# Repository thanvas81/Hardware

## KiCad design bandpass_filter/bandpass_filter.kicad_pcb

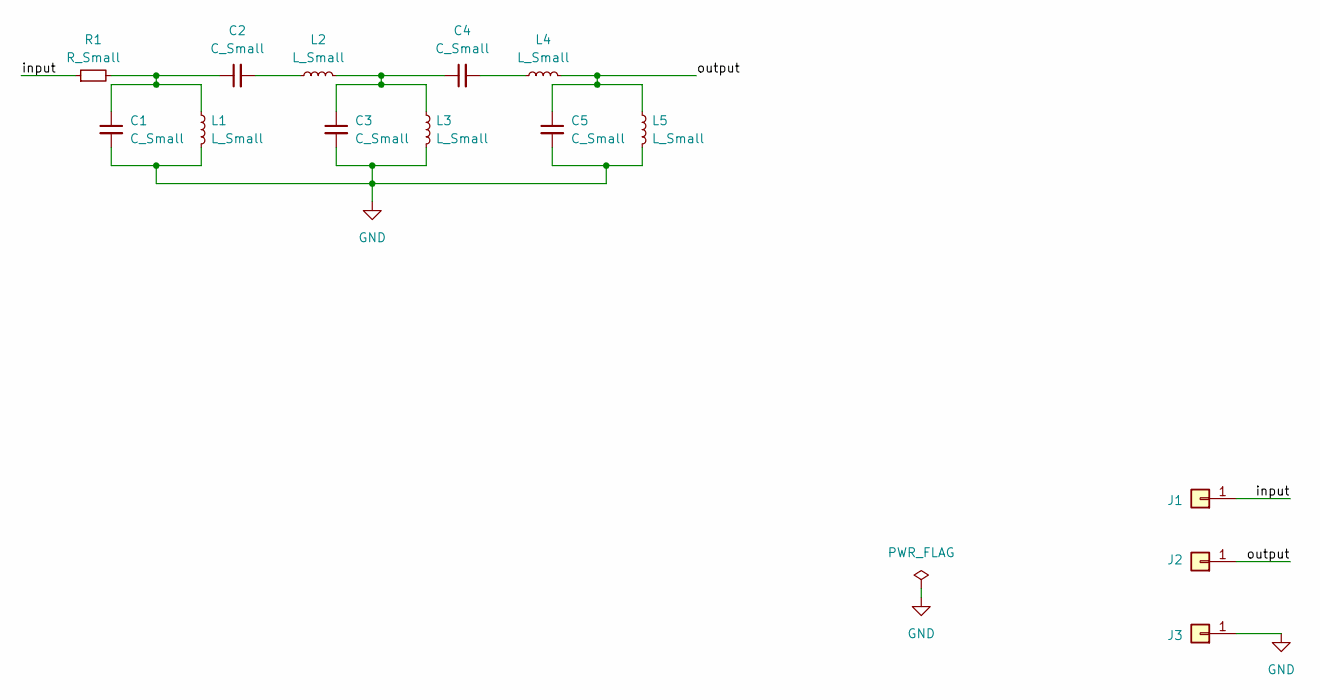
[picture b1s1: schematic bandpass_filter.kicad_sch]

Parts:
C1, C2, C3, C4, C5: C_Small; C_0603_1608Metric
J1, J2, J3: Conn_01x01; pad_smd_1.5x3
L1, L2, L3, L4, L5: L_Small; L_0603_1608Metric
R1: R_Small; R_0603_1608Metric

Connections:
/input: J1.1, R1.1
/output: C5.1, J2.1, L4.2, L5.1
GND: C1.2, C3.2, C5.2, J3.1, L1.2, L3.2, L5.2
unnamed: C1.1, C2.1, L1.1, R1.2
unnamed: C2.2, L2.1
unnamed: C3.1, C4.1, L2.2, L3.1
unnamed: C4.2, L4.1

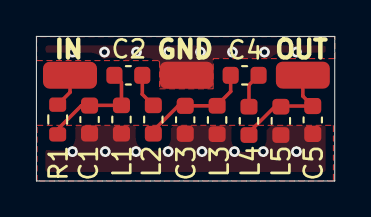
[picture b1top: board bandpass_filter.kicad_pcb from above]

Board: 2 copper layers, 16.6 x 8.0 mm, 14 parts (0 on the bottom side), 7 nets.

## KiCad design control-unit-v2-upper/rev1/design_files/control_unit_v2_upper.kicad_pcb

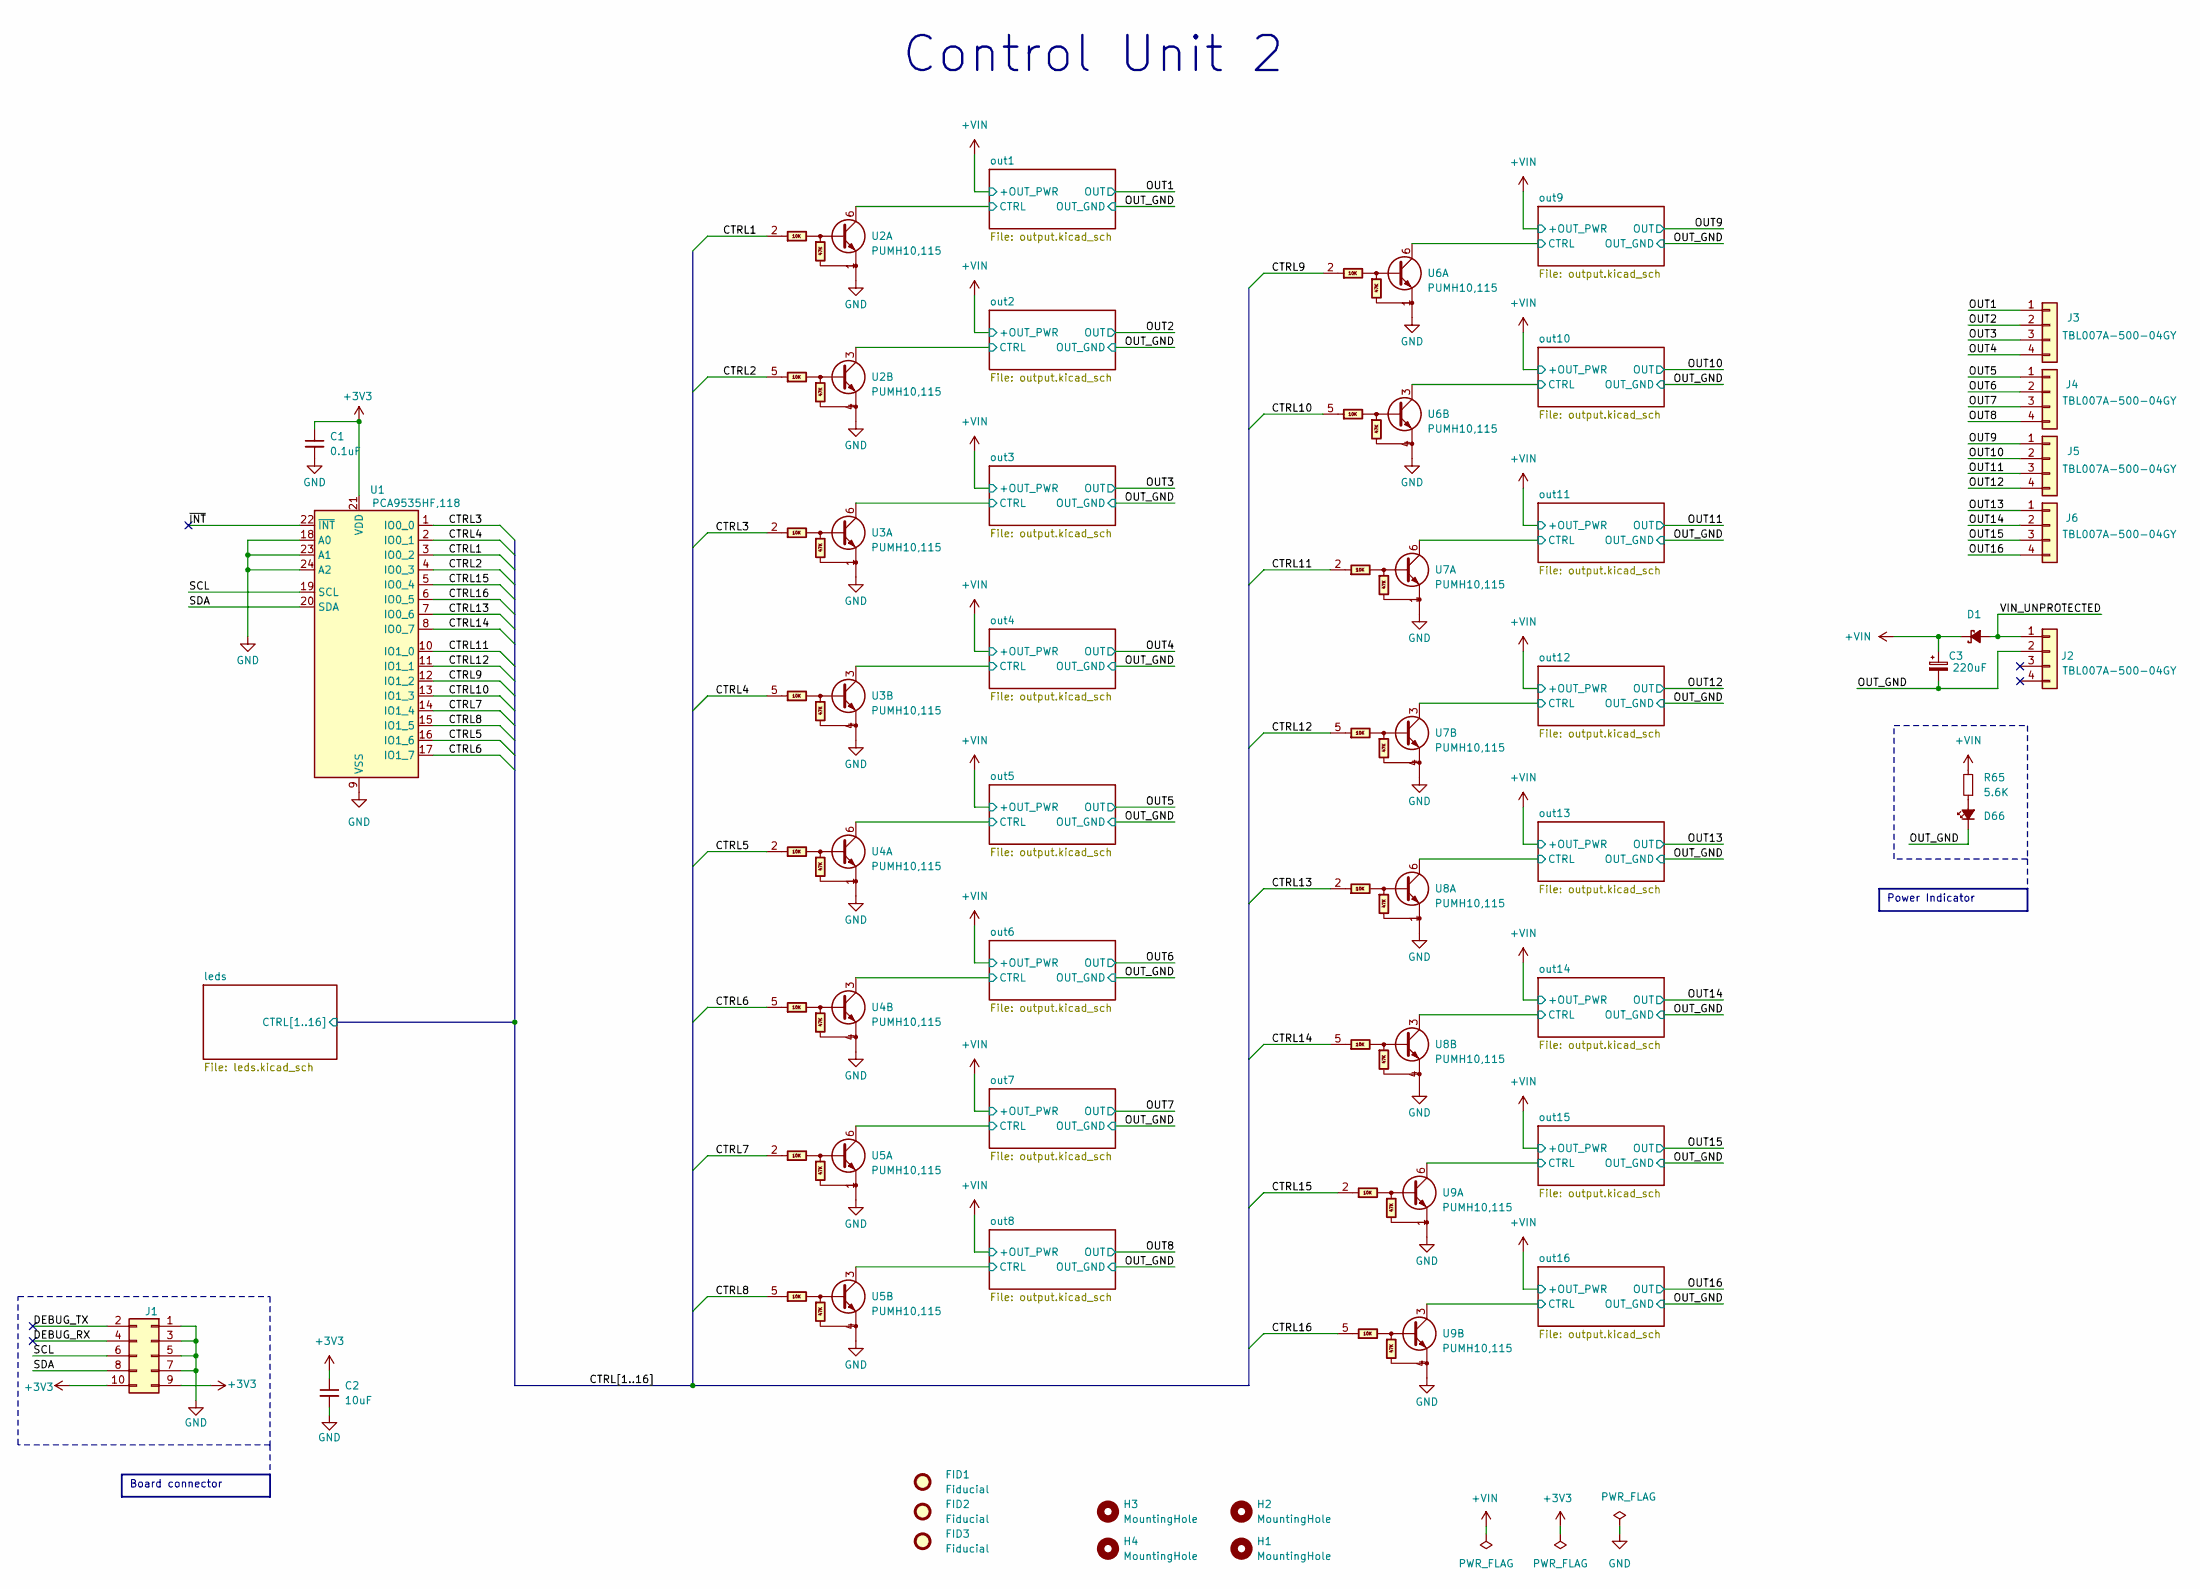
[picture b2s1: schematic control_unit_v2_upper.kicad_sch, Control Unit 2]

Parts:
C1: 0.1uF; C_0603_1608Metric; PartID 499
C2: 10uF; C_0805_2012Metric
C3: 220uF; CP_Elec_10x10
D1: D_PowerDI-123; PartID 501
D66: LED_Small_Filled; LED_0603_1608Metric; PartID 496
FID1, FID2, FID3: Fiducial; Fiducial_1mm_Mask2mm
H1, H2, H3, H4: MountingHole; MountingHole_3.2mm_M3_DIN965
J1: PinSocket_2x05_P2.54mm_Vertical_SMD
J2, J3, J4, J5, J6: TBL007A-500-04GY; TerminalBlock_IMO_203001M-4; PartID 1
R65: 5.6K; R_0402_1005Metric
U1: PCA9535HF,118; WQFN-24-1EP_4x4mm_P0.5mm_EP2.45x2.45mm; PartID 4
U2, U3, U4, U5, U6, U7, U8, U9: PUMH10,115; SOT-363_SC-70-6

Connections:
+3V3: C1.1, C2.1, J1.9, J1.10, U1.21 (VDD)
+VIN: C3.1, D1.1 (K), R65.2; also elsewhere on the board
/CTRL1: U1.3 (IO0_2), U2.2; also elsewhere on the board
/CTRL2: U1.4 (IO0_3), U2.5; also elsewhere on the board
/CTRL3: U1.1 (IO0_0), U3.2; also elsewhere on the board
/CTRL4: U1.2 (IO0_1), U3.5; also elsewhere on the board
/CTRL5: U1.16 (IO1_6), U4.2; also elsewhere on the board
/CTRL6: U1.17 (IO1_7), U4.5; also elsewhere on the board
/CTRL7: U1.14 (IO1_4), U5.2; also elsewhere on the board
/CTRL8: U1.15 (IO1_5), U5.5; also elsewhere on the board
/CTRL9: U1.12 (IO1_2), U6.2; also elsewhere on the board
/CTRL10: U1.13 (IO1_3), U6.5; also elsewhere on the board
/CTRL11: U1.10 (IO1_0), U7.2; also elsewhere on the board
/CTRL12: U1.11 (IO1_1), U7.5; also elsewhere on the board
/CTRL13: U1.7 (IO0_6), U8.2; also elsewhere on the board
/CTRL14: U1.8 (IO0_7), U8.5; also elsewhere on the board
/CTRL15: U1.5 (IO0_4), U9.2; also elsewhere on the board
/CTRL16: U1.6 (IO0_5), U9.5; also elsewhere on the board
/DEBUG_RX: J1.4
/DEBUG_TX: J1.2
/OUT1: J3.1; also elsewhere on the board
/OUT2: J3.2; also elsewhere on the board
/OUT3: J3.3; also elsewhere on the board
/OUT4: J3.4; also elsewhere on the board
/OUT5: J4.1; also elsewhere on the board
/OUT6: J4.2; also elsewhere on the board
/OUT7: J4.3; also elsewhere on the board
/OUT8: J4.4; also elsewhere on the board
/OUT9: J5.1; also elsewhere on the board
/OUT10: J5.2; also elsewhere on the board
/OUT11: J5.3; also elsewhere on the board
/OUT12: J5.4; also elsewhere on the board
/OUT13: J6.1; also elsewhere on the board
/OUT14: J6.2; also elsewhere on the board
/OUT15: J6.3; also elsewhere on the board
/OUT16: J6.4; also elsewhere on the board
/OUT_GND: C3.2, D66.1 (K), J2.2; also elsewhere on the board
/SCL: J1.6, U1.19 (SCL)
/SDA: J1.8, U1.20 (SDA)
/VIN_UNPROTECTED: D1.2 (A), J2.1
/out1/CTRL: U2.6; also elsewhere on the board
/out2/CTRL: U2.3; also elsewhere on the board
/out3/CTRL: U3.6; also elsewhere on the board
/out4/CTRL: U3.3; also elsewhere on the board
/out5/CTRL: U4.6; also elsewhere on the board
/out6/CTRL: U4.3; also elsewhere on the board
/out7/CTRL: U5.6; also elsewhere on the board
/out8/CTRL: U5.3; also elsewhere on the board
/out9/CTRL: U6.6; also elsewhere on the board
/out10/CTRL: U6.3; also elsewhere on the board
/out11/CTRL: U7.6; also elsewhere on the board
/out12/CTRL: U7.3; also elsewhere on the board
/out13/CTRL: U8.6; also elsewhere on the board
/out14/CTRL: U8.3; also elsewhere on the board
/out15/CTRL: U9.6; also elsewhere on the board
/out16/CTRL: U9.3; also elsewhere on the board
/~INT: U1.22 (~INT)
GND: C1.2, C2.2, J1.1, J1.3, J1.5, J1.7, U1.9 (VSS), U1.18 (A0), U1.23 (A1), U1.24 (A2), U1.25 (PAD), U2.1, U2.4, U3.1, U3.4, U4.1, U4.4, U5.1, U5.4, U6.1, U6.4, U7.1, U7.4, U8.1, U8.4, U9.1, U9.4; also elsewhere on the board
unnamed: D66.2 (A), R65.1

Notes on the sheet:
Power Indicator
Board connector
Control Unit 2

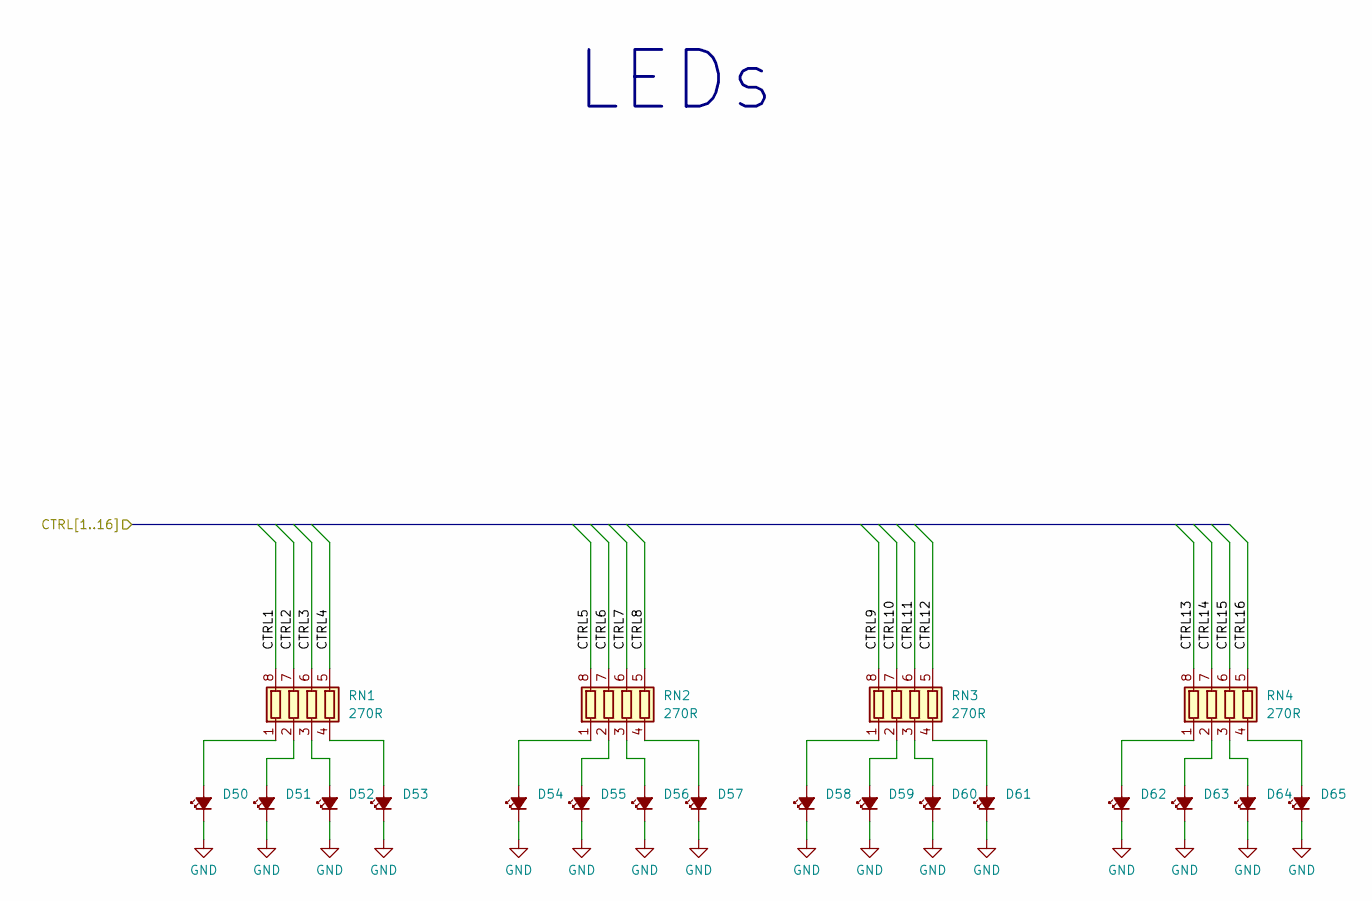
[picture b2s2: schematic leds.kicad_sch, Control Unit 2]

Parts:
D50, D51, D52, D53, D54, D55, D56, D57, D58, D59, D60, D61, D62, D63, D64, D65: LED_Small_Filled; LED_0603_1608Metric; PartID 496
RN1, RN2, RN3, RN4: 270R; R_Array_Concave_4x0603

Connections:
/CTRL1: RN1.8 (R1.2); also elsewhere on the board
/CTRL2: RN1.7 (R2.2); also elsewhere on the board
/CTRL3: RN1.6 (R3.2); also elsewhere on the board
/CTRL4: RN1.5 (R4.2); also elsewhere on the board
/CTRL5: RN2.8 (R1.2); also elsewhere on the board
/CTRL6: RN2.7 (R2.2); also elsewhere on the board
/CTRL7: RN2.6 (R3.2); also elsewhere on the board
/CTRL8: RN2.5 (R4.2); also elsewhere on the board
/CTRL9: RN3.8 (R1.2); also elsewhere on the board
/CTRL10: RN3.7 (R2.2); also elsewhere on the board
/CTRL11: RN3.6 (R3.2); also elsewhere on the board
/CTRL12: RN3.5 (R4.2); also elsewhere on the board
/CTRL13: RN4.8 (R1.2); also elsewhere on the board
/CTRL14: RN4.7 (R2.2); also elsewhere on the board
/CTRL15: RN4.6 (R3.2); also elsewhere on the board
/CTRL16: RN4.5 (R4.2); also elsewhere on the board
GND: D50.1 (K), D51.1 (K), D52.1 (K), D53.1 (K), D54.1 (K), D55.1 (K), D56.1 (K), D57.1 (K), D58.1 (K), D59.1 (K), D60.1 (K), D61.1 (K), D62.1 (K), D63.1 (K), D64.1 (K), D65.1 (K); also elsewhere on the board
unnamed: D50.2 (A), RN1.1 (R1.1)
unnamed: D51.2 (A), RN1.2 (R2.1)
unnamed: D52.2 (A), RN1.3 (R3.1)
unnamed: D53.2 (A), RN1.4 (R4.1)
unnamed: D54.2 (A), RN2.1 (R1.1)
unnamed: D55.2 (A), RN2.2 (R2.1)
unnamed: D56.2 (A), RN2.3 (R3.1)
unnamed: D57.2 (A), RN2.4 (R4.1)
unnamed: D58.2 (A), RN3.1 (R1.1)
unnamed: D59.2 (A), RN3.2 (R2.1)
unnamed: D60.2 (A), RN3.3 (R3.1)
unnamed: D61.2 (A), RN3.4 (R4.1)
unnamed: D62.2 (A), RN4.1 (R1.1)
unnamed: D63.2 (A), RN4.2 (R2.1)
unnamed: D64.2 (A), RN4.3 (R3.1)
unnamed: D65.2 (A), RN4.4 (R4.1)

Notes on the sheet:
LEDs

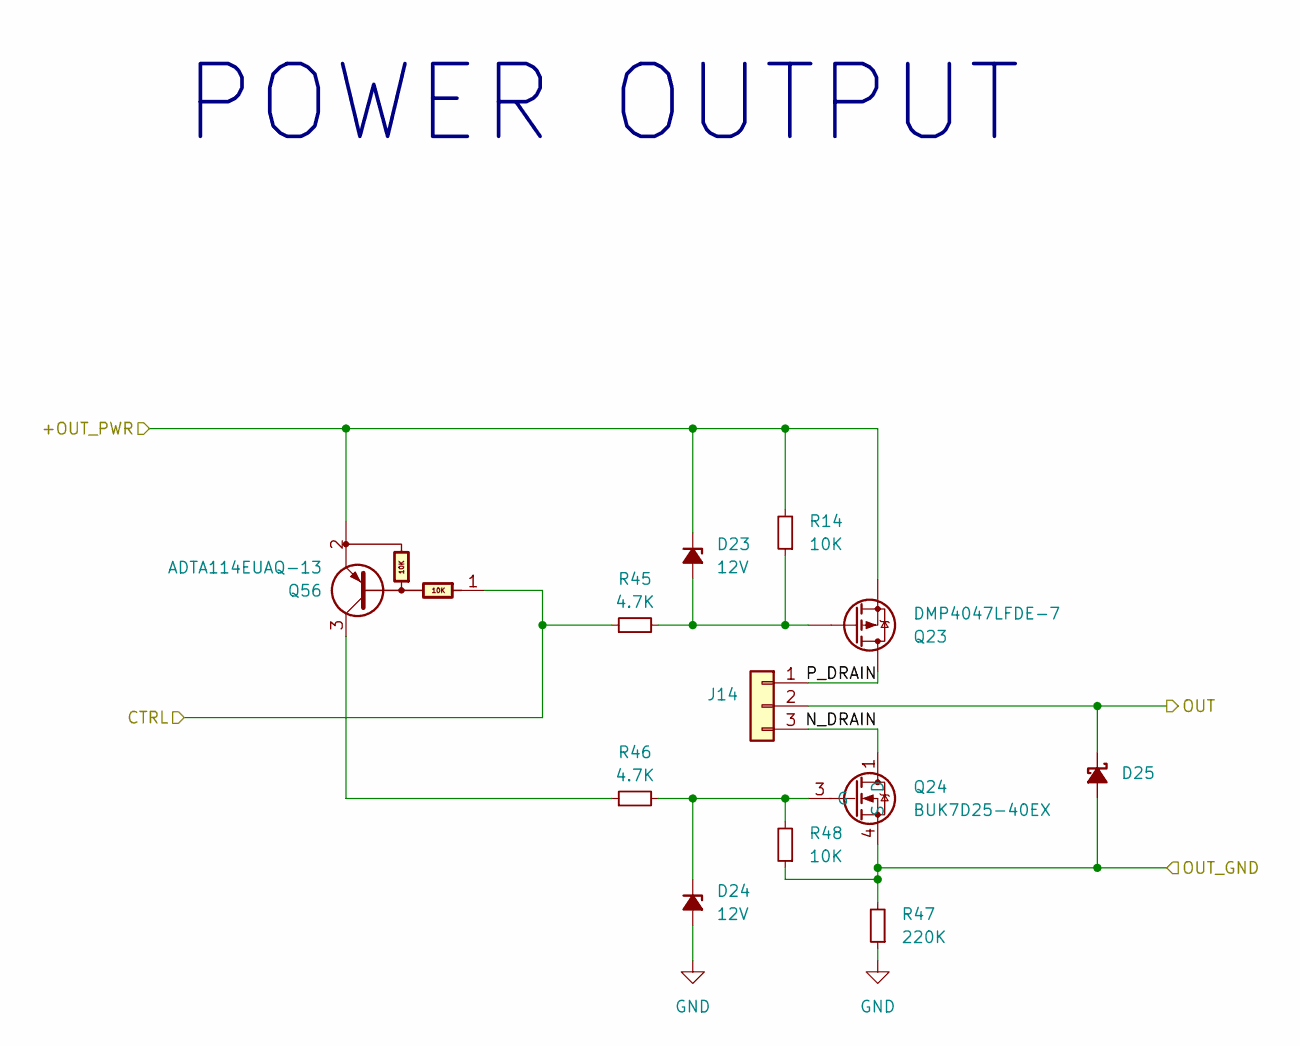
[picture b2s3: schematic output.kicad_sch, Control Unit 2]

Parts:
D23, D24: 12V; D_SOD-323
D25: D_PowerDI-123; PartID 501
J14: PinHeader_1x03_P2.54mm_Vertical
Q23: DMP4047LFDE-7; Diodes_Inc_U-DFN2020-6 (Type E)
Q24: BUK7D25-40EX; Diodes_UDFN2020-6_Type-F
Q56: ADTA114EUAQ-13; SOT-323_SC-70
R14, R48: 10K; R_0402_1005Metric
R45, R46: 4.7K; R_0402_1005Metric
R47: 220K; R_0402_1005Metric

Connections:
+VIN: D23.1 (K), Q23.3 (S), Q56.2, R14.2; also elsewhere on the board
/OUT8: D25.1 (K), J14.2; also elsewhere on the board
/OUT_GND: D25.2 (A), Q24.4 (S), Q24.8 (S), R47.2, R48.1; also elsewhere on the board
/out8/CTRL: Q56.1, R45.1; also elsewhere on the board
/out8/N_DRAIN: J14.3, Q24.1 (D), Q24.2 (D), Q24.5 (D), Q24.6 (D), Q24.7 (D)
/out8/P_DRAIN: J14.1, Q23.1 (D)
GND: D24.2 (A), R47.1; also elsewhere on the board
unnamed: D23.2 (A), Q23.2 (G), R14.1, R45.2
unnamed: D24.1 (K), Q24.3 (G), R46.2, R48.2
unnamed: Q56.3, R46.1

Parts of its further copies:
D2, D3, D5, D6, D8, D9, D11, D12, D14, D15, D17, D18, D20, D21, D26, D27, D29, D30, D32, D33, D35, D36, D38, D39, D41, D42, D44, D45, D47, D48: 12V; D_SOD-323
D4, D7, D10, D13, D16, D19, D22, D28, D31, D34, D37, D40, D43, D46, D49: D_PowerDI-123; PartID 501
J7, J8, J9, J10, J11, J12, J13, J15, J16, J17, J18, J19, J20, J21, J22: PinHeader_1x03_P2.54mm_Vertical
Q1, Q50, Q51, Q52, Q53, Q54, Q55, Q57, Q58, Q59, Q60, Q61, Q62, Q63, Q64: ADTA114EUAQ-13; SOT-323_SC-70
Q2, Q5, Q8, Q11, Q14, Q17, Q20, Q26, Q29, Q32, Q35, Q38, Q41, Q44, Q47: DMP4047LFDE-7; Diodes_Inc_U-DFN2020-6 (Type E)
Q3, Q6, Q9, Q12, Q15, Q18, Q21, Q27, Q30, Q33, Q36, Q39, Q42, Q45, Q48: BUK7D25-40EX; Diodes_UDFN2020-6_Type-F
R1, R2, R9, R10, R15, R16, R21, R22, R27, R28, R33, R34, R39, R40, R51, R52, R57, R58, R63, R64, R69, R70, R75, R76, R81, R82, R87, R88, R93, R94: 4.7K; R_0402_1005Metric
R3, R4, R5, R6, R7, R8, R11, R12, R13, R17, R18, R19, R20, R23, R24, R25, R26, R29, R30, R31, R36, R42, R54, R60, R66, R72, R78, R84, R90, R96: 10K; R_0402_1005Metric
R32, R35, R37, R38, R41, R43, R44, R49, R50, R53, R55, R56, R59, R61, R62: 220K; R_0402_1005Metric

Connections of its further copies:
+VIN: D2.1 (K), D5.1 (K), D8.1 (K), D11.1 (K), D14.1 (K), D17.1 (K), D20.1 (K), D26.1 (K), D29.1 (K), D32.1 (K), D35.1 (K), D38.1 (K), D41.1 (K), D44.1 (K), D47.1 (K), Q1.2, Q2.3 (S), Q5.3 (S), Q8.3 (S), Q11.3 (S), Q14.3 (S), Q17.3 (S), Q20.3 (S), Q26.3 (S), Q29.3 (S), Q32.3 (S), Q35.3 (S), Q38.3 (S), Q41.3 (S), Q44.3 (S), Q47.3 (S), Q50.2, Q51.2, Q52.2, Q53.2, Q54.2, Q55.2, Q57.2, Q58.2, Q59.2, Q60.2, Q61.2, Q62.2, Q63.2, Q64.2, R3.2, R5.2, R6.2, R7.2, R8.2, R11.2, R13.2, R17.2, R19.2, R20.2, R23.2, R25.2, R26.2, R29.2, R31.2; also elsewhere on the board
/OUT1: D4.1 (K), J7.2; also elsewhere on the board
/OUT2: D7.1 (K), J8.2; also elsewhere on the board
/OUT3: D10.1 (K), J9.2; also elsewhere on the board
/OUT4: D13.1 (K), J10.2; also elsewhere on the board
/OUT5: D16.1 (K), J11.2; also elsewhere on the board
/OUT6: D19.1 (K), J12.2; also elsewhere on the board
/OUT7: D22.1 (K), J13.2; also elsewhere on the board
/OUT9: D28.1 (K), J15.2; also elsewhere on the board
/OUT10: D31.1 (K), J16.2; also elsewhere on the board
/OUT11: D34.1 (K), J17.2; also elsewhere on the board
/OUT12: D37.1 (K), J18.2; also elsewhere on the board
/OUT13: D40.1 (K), J19.2; also elsewhere on the board
/OUT14: D43.1 (K), J20.2; also elsewhere on the board
/OUT15: D46.1 (K), J21.2; also elsewhere on the board
/OUT16: D49.1 (K), J22.2; also elsewhere on the board
/OUT_GND: D4.2 (A), D7.2 (A), D10.2 (A), D13.2 (A), D16.2 (A), D19.2 (A), D22.2 (A), D28.2 (A), D31.2 (A), D34.2 (A), D37.2 (A), D40.2 (A), D43.2 (A), D46.2 (A), D49.2 (A), Q3.4 (S), Q3.8 (S), Q6.4 (S), Q6.8 (S), Q9.4 (S), Q9.8 (S), Q12.4 (S), Q12.8 (S), Q15.4 (S), Q15.8 (S), Q18.4 (S), Q18.8 (S), Q21.4 (S), Q21.8 (S), Q27.4 (S), Q27.8 (S), Q30.4 (S), Q30.8 (S), Q33.4 (S), Q33.8 (S), Q36.4 (S), Q36.8 (S), Q39.4 (S), Q39.8 (S), Q42.4 (S), Q42.8 (S), Q45.4 (S), Q45.8 (S), Q48.4 (S), Q48.8 (S), R4.1, R12.1, R18.1, R24.1, R30.1, R32.2, R35.2, R36.1, R37.2, R38.2, R41.2, R42.1, R43.2, R44.2, R49.2, R50.2, R53.2, R54.1, R55.2, R56.2, R59.2, R60.1, R61.2, R62.2, R66.1, R72.1, R78.1, R84.1, R90.1, R96.1; also elsewhere on the board
/out1/CTRL: Q1.1, R1.1; also elsewhere on the board
/out1/N_DRAIN: J7.3, Q3.1 (D), Q3.2 (D), Q3.5 (D), Q3.6 (D), Q3.7 (D)
/out1/P_DRAIN: J7.1, Q2.1 (D)
/out2/CTRL: Q51.1, R9.1; also elsewhere on the board
/out2/N_DRAIN: J8.3, Q6.1 (D), Q6.2 (D), Q6.5 (D), Q6.6 (D), Q6.7 (D)
/out2/P_DRAIN: J8.1, Q5.1 (D)
/out3/CTRL: Q50.1, R15.1; also elsewhere on the board
/out3/N_DRAIN: J9.3, Q9.1 (D), Q9.2 (D), Q9.5 (D), Q9.6 (D), Q9.7 (D)
/out3/P_DRAIN: J9.1, Q8.1 (D)
/out4/CTRL: Q52.1, R21.1; also elsewhere on the board
/out4/N_DRAIN: J10.3, Q12.1 (D), Q12.2 (D), Q12.5 (D), Q12.6 (D), Q12.7 (D)
/out4/P_DRAIN: J10.1, Q11.1 (D)
/out5/CTRL: Q53.1, R27.1; also elsewhere on the board
/out5/N_DRAIN: J11.3, Q15.1 (D), Q15.2 (D), Q15.5 (D), Q15.6 (D), Q15.7 (D)
/out5/P_DRAIN: J11.1, Q14.1 (D)
/out6/CTRL: Q54.1, R33.1; also elsewhere on the board
/out6/N_DRAIN: J12.3, Q18.1 (D), Q18.2 (D), Q18.5 (D), Q18.6 (D), Q18.7 (D)
/out6/P_DRAIN: J12.1, Q17.1 (D)
/out7/CTRL: Q55.1, R39.1; also elsewhere on the board
/out7/N_DRAIN: J13.3, Q21.1 (D), Q21.2 (D), Q21.5 (D), Q21.6 (D), Q21.7 (D)
/out7/P_DRAIN: J13.1, Q20.1 (D)
/out9/CTRL: Q57.1, R51.1; also elsewhere on the board
/out9/N_DRAIN: J15.3, Q27.1 (D), Q27.2 (D), Q27.5 (D), Q27.6 (D), Q27.7 (D)
/out9/P_DRAIN: J15.1, Q26.1 (D)
/out10/CTRL: Q58.1, R57.1; also elsewhere on the board
/out10/N_DRAIN: J16.3, Q30.1 (D), Q30.2 (D), Q30.5 (D), Q30.6 (D), Q30.7 (D)
/out10/P_DRAIN: J16.1, Q29.1 (D)
/out11/CTRL: Q59.1, R63.1; also elsewhere on the board
/out11/N_DRAIN: J17.3, Q33.1 (D), Q33.2 (D), Q33.5 (D), Q33.6 (D), Q33.7 (D)
/out11/P_DRAIN: J17.1, Q32.1 (D)
/out12/CTRL: Q60.1, R69.1; also elsewhere on the board
/out12/N_DRAIN: J18.3, Q36.1 (D), Q36.2 (D), Q36.5 (D), Q36.6 (D), Q36.7 (D)
/out12/P_DRAIN: J18.1, Q35.1 (D)
/out13/CTRL: Q61.1, R75.1; also elsewhere on the board
/out13/N_DRAIN: J19.3, Q39.1 (D), Q39.2 (D), Q39.5 (D), Q39.6 (D), Q39.7 (D)
/out13/P_DRAIN: J19.1, Q38.1 (D)
/out14/CTRL: Q62.1, R81.1; also elsewhere on the board
/out14/N_DRAIN: J20.3, Q42.1 (D), Q42.2 (D), Q42.5 (D), Q42.6 (D), Q42.7 (D)
/out14/P_DRAIN: J20.1, Q41.1 (D)
/out15/CTRL: Q63.1, R87.1; also elsewhere on the board
/out15/N_DRAIN: J21.3, Q45.1 (D), Q45.2 (D), Q45.5 (D), Q45.6 (D), Q45.7 (D)
/out15/P_DRAIN: J21.1, Q44.1 (D)
/out16/CTRL: Q64.1, R93.1; also elsewhere on the board
/out16/N_DRAIN: J22.3, Q48.1 (D), Q48.2 (D), Q48.5 (D), Q48.6 (D), Q48.7 (D)
/out16/P_DRAIN: J22.1, Q47.1 (D)
GND: D3.2 (A), D6.2 (A), D9.2 (A), D12.2 (A), D15.2 (A), D18.2 (A), D21.2 (A), D27.2 (A), D30.2 (A), D33.2 (A), D36.2 (A), D39.2 (A), D42.2 (A), D45.2 (A), D48.2 (A), R32.1, R35.1, R37.1, R38.1, R41.1, R43.1, R44.1, R49.1, R50.1, R53.1, R55.1, R56.1, R59.1, R61.1, R62.1; also elsewhere on the board
unnamed: D2.2 (A), Q2.2 (G), R1.2, R3.1
unnamed: D3.1 (K), Q3.3 (G), R2.2, R4.2
unnamed: D5.2 (A), Q5.2 (G), R6.1, R9.2
unnamed: D6.1 (K), Q6.3 (G), R10.2, R12.2
unnamed: D8.2 (A), Q8.2 (G), R5.1, R15.2
unnamed: D9.1 (K), Q9.3 (G), R16.2, R18.2
unnamed: D11.2 (A), Q11.2 (G), R7.1, R21.2
unnamed: D12.1 (K), Q12.3 (G), R22.2, R24.2
unnamed: D14.2 (A), Q14.2 (G), R8.1, R27.2
unnamed: D15.1 (K), Q15.3 (G), R28.2, R30.2
unnamed: D17.2 (A), Q17.2 (G), R11.1, R33.2
unnamed: D18.1 (K), Q18.3 (G), R34.2, R36.2
unnamed: D20.2 (A), Q20.2 (G), R13.1, R39.2
unnamed: D21.1 (K), Q21.3 (G), R40.2, R42.2
unnamed: D26.2 (A), Q26.2 (G), R17.1, R51.2
unnamed: D27.1 (K), Q27.3 (G), R52.2, R54.2
unnamed: D29.2 (A), Q29.2 (G), R19.1, R57.2
unnamed: D30.1 (K), Q30.3 (G), R58.2, R60.2
unnamed: D32.2 (A), Q32.2 (G), R20.1, R63.2
unnamed: D33.1 (K), Q33.3 (G), R64.2, R66.2
unnamed: D35.2 (A), Q35.2 (G), R23.1, R69.2
unnamed: D36.1 (K), Q36.3 (G), R70.2, R72.2
unnamed: D38.2 (A), Q38.2 (G), R25.1, R75.2
unnamed: D39.1 (K), Q39.3 (G), R76.2, R78.2
unnamed: D41.2 (A), Q41.2 (G), R26.1, R81.2
unnamed: D42.1 (K), Q42.3 (G), R82.2, R84.2
unnamed: D44.2 (A), Q44.2 (G), R29.1, R87.2
unnamed: D45.1 (K), Q45.3 (G), R88.2, R90.2
unnamed: D47.2 (A), Q47.2 (G), R31.1, R93.2
unnamed: D48.1 (K), Q48.3 (G), R94.2, R96.2
unnamed: Q1.3, R2.1
unnamed: Q50.3, R16.1
unnamed: Q51.3, R10.1
unnamed: Q52.3, R22.1
unnamed: Q53.3, R28.1
unnamed: Q54.3, R34.1
unnamed: Q55.3, R40.1
unnamed: Q57.3, R52.1
unnamed: Q58.3, R58.1
unnamed: Q59.3, R64.1
unnamed: Q60.3, R70.1
unnamed: Q61.3, R76.1
unnamed: Q62.3, R82.1
unnamed: Q63.3, R88.1
unnamed: Q64.3, R94.1

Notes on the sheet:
POWER OUTPUT

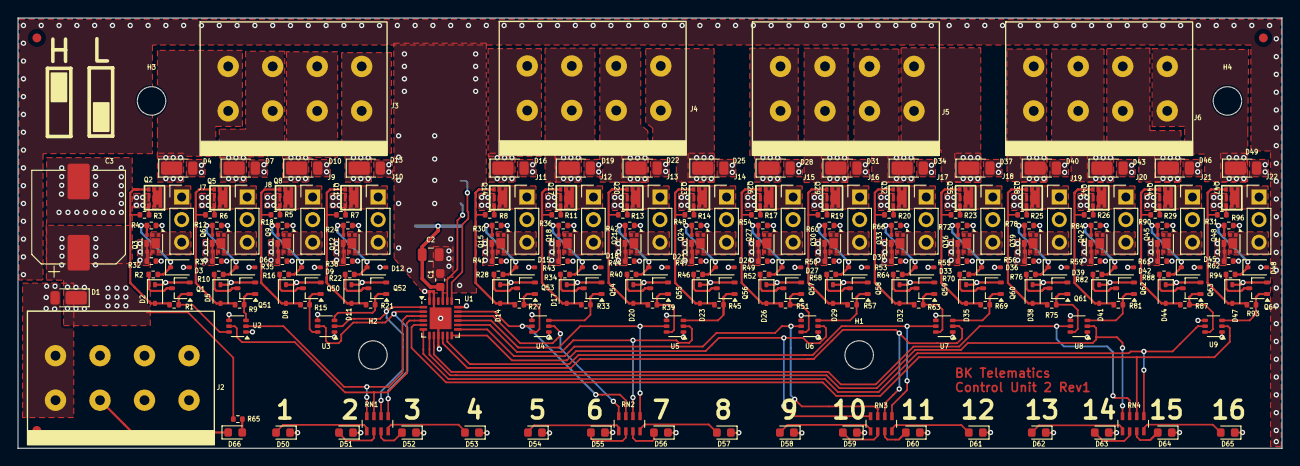
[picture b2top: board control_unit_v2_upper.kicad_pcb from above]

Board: 4 copper layers, 142.0 x 48.3 mm, 240 parts (1 on the bottom side), 152 nets.

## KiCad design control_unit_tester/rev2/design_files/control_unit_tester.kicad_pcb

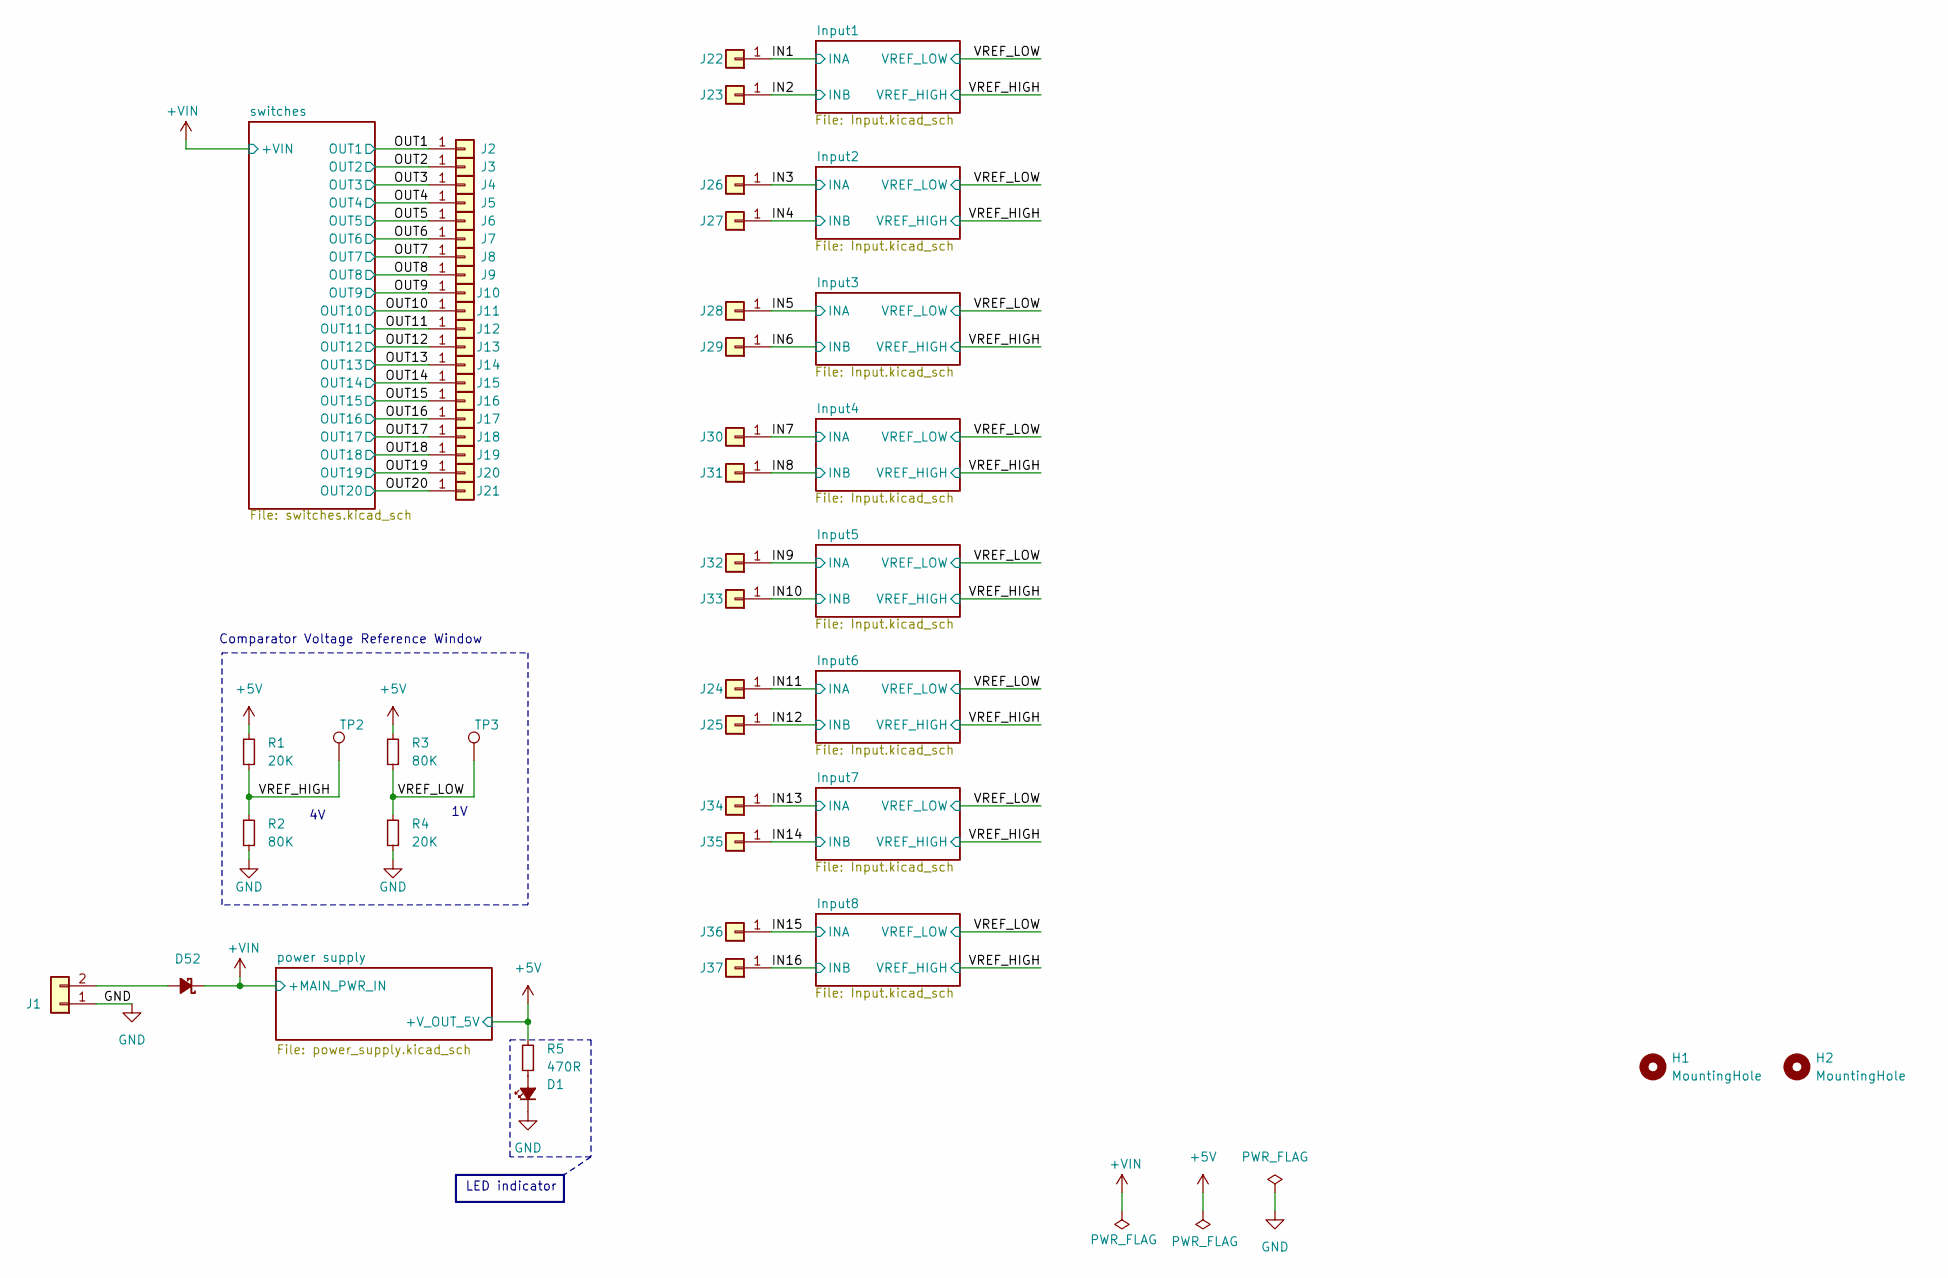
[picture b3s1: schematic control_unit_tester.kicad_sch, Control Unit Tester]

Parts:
D1: LED 0805 SMD; LED_0805_2012Metric
D52: SBR3U60P1Q-7; D_PowerDI-123; PartkeeprID 43
H1, H2: MountingHole; MountingHole_3.2mm_M3_DIN965
J1: Conn_01x02; TerminalBlock_4Ucon_1x02_P3.50mm_Horizontal
J2, J3, J4, J5, J6, J7, J8, J9, J10, J11, J12, J13, J14, J15, J16, J17, J18, J19, J20, J21, J22, J23, J24, J25, J26, J27, J28, J29, J30, J31, J32, J33, J34, J35, J36, J37: T.H. Pad; Hole_pad_1.5x3_round
R1, R4: 20Κ; R_0805_2012Metric
R2, R3: 80Κ; R_0805_2012Metric
R5: 470R; R_0805_2012Metric
TP2, TP3: TestPoint; TestPoint_Pad_D1.5mm

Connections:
+5V: R1.1, R3.1, R5.2; also elsewhere on the board
+VIN: D52.1 (K); also elsewhere on the board
/IN1: J22.1; also elsewhere on the board
/IN2: J23.1; also elsewhere on the board
/IN3: J26.1; also elsewhere on the board
/IN4: J27.1; also elsewhere on the board
/IN5: J28.1; also elsewhere on the board
/IN6: J29.1; also elsewhere on the board
/IN7: J30.1; also elsewhere on the board
/IN8: J31.1; also elsewhere on the board
/IN9: J32.1; also elsewhere on the board
/IN10: J33.1; also elsewhere on the board
/IN11: J24.1; also elsewhere on the board
/IN12: J25.1; also elsewhere on the board
/IN13: J34.1; also elsewhere on the board
/IN14: J35.1; also elsewhere on the board
/IN15: J36.1; also elsewhere on the board
/IN16: J37.1; also elsewhere on the board
/OUT1: J2.1; also elsewhere on the board
/OUT2: J3.1; also elsewhere on the board
/OUT3: J4.1; also elsewhere on the board
/OUT4: J5.1; also elsewhere on the board
/OUT5: J6.1; also elsewhere on the board
/OUT6: J7.1; also elsewhere on the board
/OUT7: J8.1; also elsewhere on the board
/OUT8: J9.1; also elsewhere on the board
/OUT9: J10.1; also elsewhere on the board
/OUT10: J11.1; also elsewhere on the board
/OUT11: J12.1; also elsewhere on the board
/OUT12: J13.1; also elsewhere on the board
/OUT13: J14.1; also elsewhere on the board
/OUT14: J15.1; also elsewhere on the board
/OUT15: J16.1; also elsewhere on the board
/OUT16: J17.1; also elsewhere on the board
/OUT17: J18.1; also elsewhere on the board
/OUT18: J19.1; also elsewhere on the board
/OUT19: J20.1; also elsewhere on the board
/OUT20: J21.1; also elsewhere on the board
/VREF_HIGH: R1.2, R2.1, TP2.1; also elsewhere on the board
/VREF_LOW: R3.2, R4.1, TP3.1; also elsewhere on the board
GND: D1.1 (K), J1.1, R2.2, R4.2; also elsewhere on the board
unnamed: D1.2 (A), R5.1
unnamed: D52.2 (A), J1.2

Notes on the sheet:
LED indicator
Comparator Voltage Reference Window

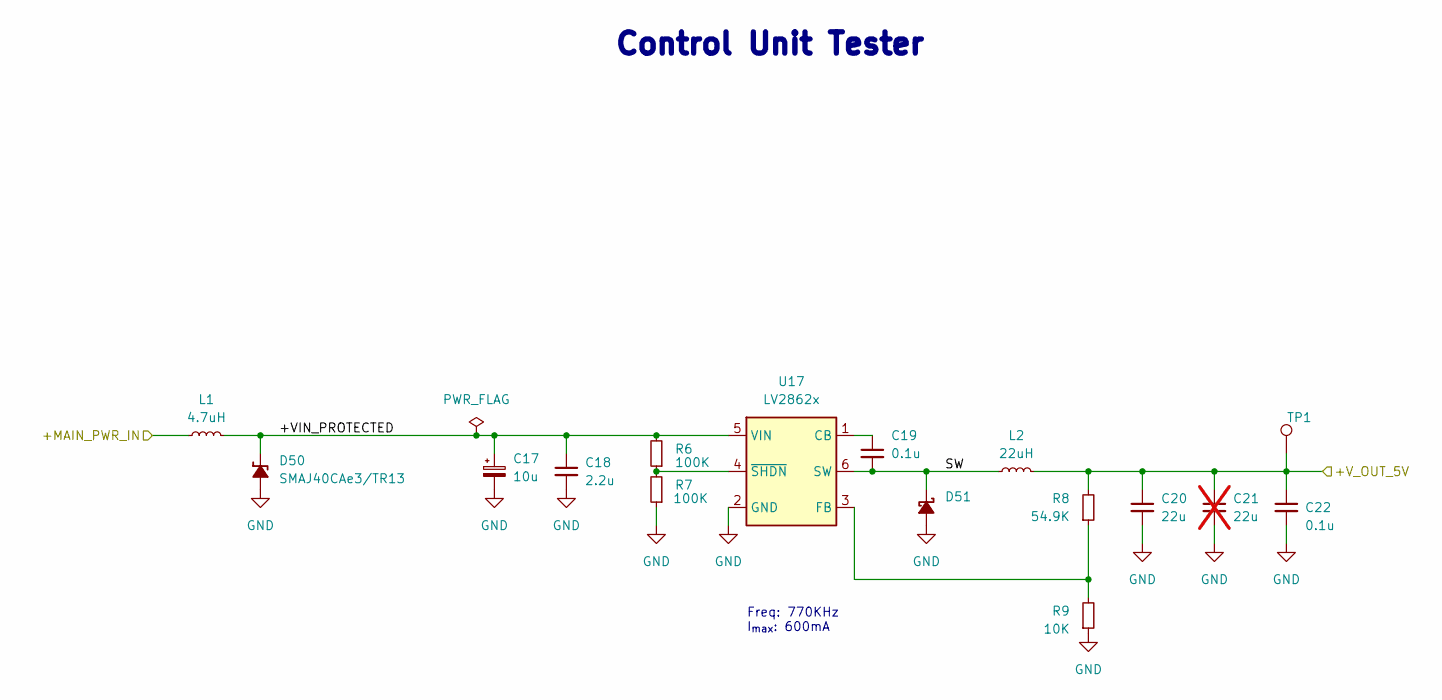
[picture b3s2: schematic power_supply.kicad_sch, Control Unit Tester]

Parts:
C17: 10u; CP_Elec_5x5.3; PartkeeprID 41
C18: 2.2u; C_1210_3225Metric; PartkeeprID 42
C19, C22: 0.1u; C_0603_1608Metric; PartkeeprID 50
C20: 22u; C_1210_3225Metric; PartkeeprID 45
C21: 22u; C_1210_3225Metric; PartkeeprID 45; not fitted
D50: SMAJ40CAe3/TR13; D_SMA
D51: SBR3U60P1Q-7; D_PowerDI-123; PartkeeprID 43
L1: 4.7uH; L_TDK_VLS252012HBX; PartkeeprID 44
L2: 22uH; L_Taiyo-Yuden_NR-50xx; PartkeeprID 44
R6, R7: 100K; R_0603_1608Metric; PartkeeprID 47
R8: 54.9K; R_0603_1608Metric; PartkeeprID 49
R9: 10K; R_0603_1608Metric; PartkeeprID 48
TP1: TestPoint; TestPoint_Pad_D1.5mm
U17: LV2862x; SOT-23-6; PartkeeprID 46

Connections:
+5V: C20.1, C21.1, C22.1, L2.2, R8.2, TP1.1; also elsewhere on the board
+VIN: L1.1; also elsewhere on the board
/power supply/+VIN_PROTECTED: C17.1, C18.1, D50.1 (K), L1.2, R6.2, U17.5 (VIN)
/power supply/SW: C19.2, D51.1 (K), L2.1, U17.6 (SW)
GND: C17.2, C18.2, C20.2, C21.2, C22.2, D50.2 (A), D51.2 (A), R7.1, R9.1, U17.2 (GND); also elsewhere on the board
unnamed: C19.1, U17.1 (CB)
unnamed: R8.1, R9.2, U17.3 (FB)
unnamed: R6.1, R7.2, U17.4 (~SHDN)

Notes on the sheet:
${TITLE}
Freq: 770KHz I_{max}: 600mA
